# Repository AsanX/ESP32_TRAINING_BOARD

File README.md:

# ESP32_TRAINING_BOARD

ESP32 Training board is designed to have multiple things to play with so there are lot's of opportunities to learn the ESP32.
I made this board so i can remotely open our front door from 4th floor and figured i could do something else with it too.

- USB-C Charging, programming and serial monitor
- 18650 Battery with commonly used TP4056 charging circuit
- RGB Led
- Button / Encoder
- TMP100 12Bit I2C Temperature sensor
- OLED I2C Display
- Few optocoupler for inputs and outputs

# Alredy found mistakes from HW 1.0
## Enable pin and auto reset
When using automatic reset for programming, there needs to be a uF range capacitor on enable.
This is to make sure the IO0 pin is given some time to pull low to enter the download mode before the en pin gets HIGH.

## TP4056 temperature pin
Datasheet clearly says that the pin should be pulled low if there are no temperature sensor on the battery

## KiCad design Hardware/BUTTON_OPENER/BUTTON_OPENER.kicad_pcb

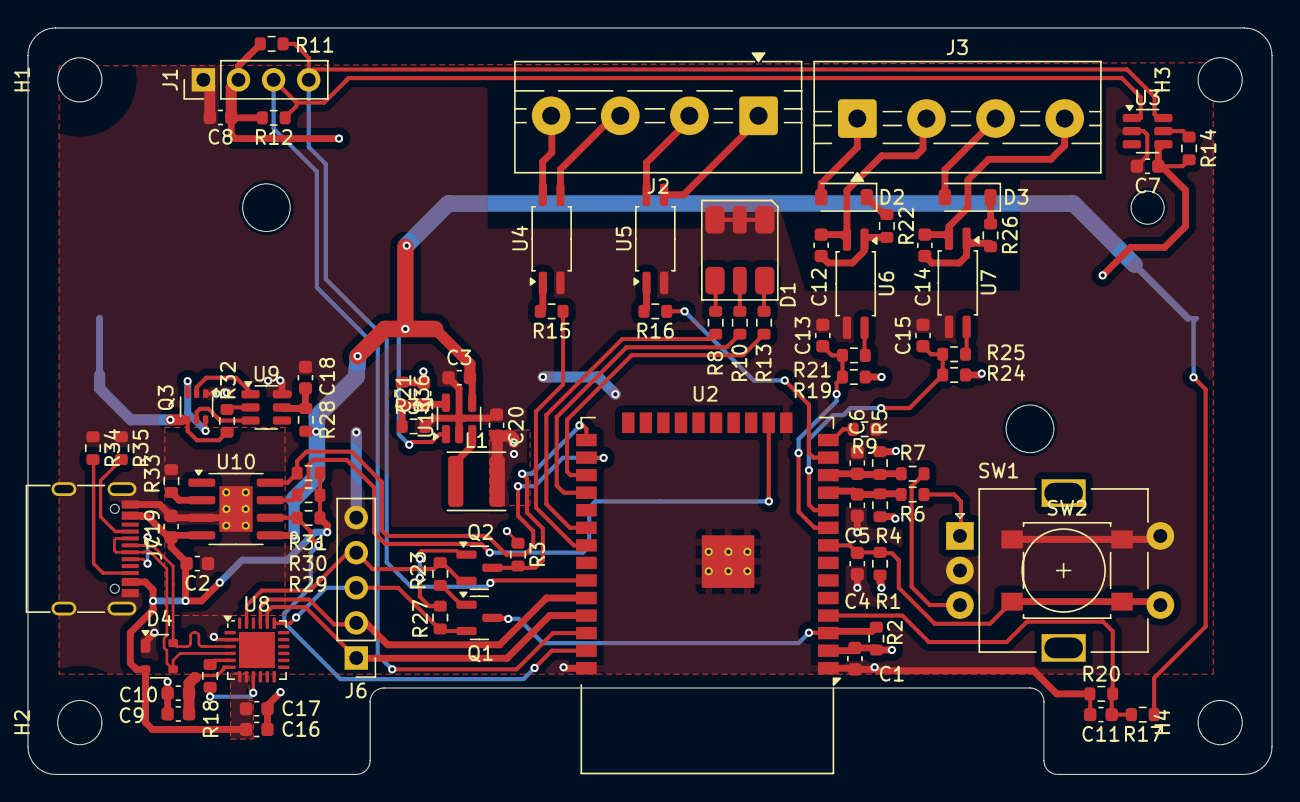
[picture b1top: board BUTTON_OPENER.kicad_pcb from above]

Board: 2 copper layers, 90.0 x 54.0 mm, 88 parts (1 on the bottom side), 67 nets.

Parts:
BT1: 18650 holder; BatteryHolder_Keystone_1042_1x18650
C1, C3, C20: 10uF 6.3V X7R; C_0603_1608Metric
C2: 1uF 10V X7R; C_0603_1608Metric
C4, C5, C6, C7, C8, C10, C11, C12, C13, C14, C15, C17, C18, C19: 100nF 10V X7R; C_0603_1608Metric
C9, C16: 4.7uF 10V X7R; C_0603_1608Metric
C21: 22pF; C_0603_1608Metric
D1: Inolux_IN-P55TATRGB; LED_Inolux_IN-P55TATRGB_PLCC6_5.0x5.5mm_P1.8mm
D2, D3: D; D_SOD-123
D4: SP0503BAHT; SOT-143
H1, H2, H3, H4: MountingHole; MountingHole_3.2mm_M3
J1: N/A; PinHeader_1x04_P2.54mm_Vertical
J2, J3: Screw_Terminal_01x04; TerminalBlock_MaiXu_MX126-5.0-04P_1x04_P5.00mm
J6: Conn_01x05; PinHeader_1x05_P2.54mm_Vertical
J7: USB_C_Receptacle_USB2.0_14P; USB_C_Receptacle_G-Switch_GT-USB-7010ASV
L1: 2.2uH; L_APV_ANR4020
Q1, Q2: BC847; SOT-23
Q3: BSD840N; SOT-363_SC-70-6
R1, R22, R26: 10K; R_0603_1608Metric
R2, R3, R9, R17: 33K; R_0603_1608Metric
R4, R5: 6K8; R_0603_1608Metric
R6, R7, R8, R13, R15, R16, R18, R21, R25, R32: 1K; R_0603_1608Metric
R10: 1K5; R_0603_1608Metric
R11, R12: 3K3; R_0603_1608Metric
R14, R19, R24, R29, R30: 47K; R_0603_1608Metric
R20: 8K2; R_0603_1608Metric
R23, R27: 12K; R_0603_1608Metric
R28: 100R; R_0603_1608Metric
R31: 0R; R_0603_1608Metric
R33: 2K2; R_0603_1608Metric
R34, R35: 5K1; R_0603_1608Metric
R36: 540K; R_0603_1608Metric
R37: 120K; R_0603_1608Metric
SW1: N/A; RotaryEncoder_Alps_EC11E-Switch_Vertical_H20mm
SW2: SW_Push; SW_SPST_B3S-1000
U2: ESP32-WROOM; ESP32-WROOM-32D
U3: TMP100; SOT-23-6
U4, U5, U6, U7: TCMT1100; SOP-4_4.4x2.6mm_P1.27mm
U8: CP2102N; QFN-24-1EP_4x4mm_P0.5mm_EP2.6x2.6mm
U9: DW01A; SOT-23-6
U10: TP4056-42-ESOP8; SOIC-8-1EP_3.9x4.9mm_P1.27mm_EP2.41x3.3mm_ThermalVias
U11: SUNTEK SK6615CS5; SOT-23-5

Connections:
+3V3: C1.2, C7.1, C8.1, C20.2, C21.2, J1.2, L1.2, R1.1, R2.1, R3.1, R4.1, R5.1, R11.2, R12.2, R14.2, R19.2, R24.2, R36.1, U2.2 (VDD), U3.4 (V+)
/B: R13.1, U2.27 (IO16)
/CHRG: R30.1, U2.16 (IO13), U10.7 (~CHRG)
/D+: D4.4 (K), J7.A6 (D+), J7.B6 (D+), U8.3 (D+)
/D-: D4.3 (K), J7.A7 (D-), J7.B7 (D-), U8.4 (D-)
/DTR: J6.4, Q2.2 (E), R23.1, U8.23 (~DTR)
/EN: R31.1, U2.26 (IO4), U10.8 (CE)
/ENABLE: Q1.3 (C), R2.2, U2.3 (EN)
/ENC_A: C5.2, R4.2, R6.2, U2.11 (IO26)
/ENC_B: C6.2, R5.2, R7.2, U2.12 (IO27)
/ENC_SW: C4.2, R1.2, SW1.S1, SW2.2, U2.8 (IO32)
/G: R10.1, U2.28 (IO17)
/GPIO0: Q2.3 (C), R3.2, U2.25 (IO0)
/OPTO_1: R15.1, U2.31 (IO19)
/OPTO_2: R16.1, U2.13 (IO14)
/OPTO_IN1: C13.1, R19.1, R21.2, U2.9 (IO33)
/OPTO_IN2: C15.1, R24.1, R25.2, U2.10 (IO25)
/R: R8.1, U2.30 (IO18)
/RTS: J6.3, Q1.2 (E), R27.1, U8.19 (~RTS)
/RXD: J6.2, U2.34 (RXD0/IO3), U8.21 (TXD)
/SCL: J1.3, R12.1, U2.36 (IO22), U3.1 (SCL)
/SDA: J1.4, R11.1, U2.33 (IO21), U3.6 (SDA)
/STDBY: R29.1, U2.37 (IO23), U10.6 (~STDBY)
/TXD: J6.1, U2.35 (TXD0/IO1), U8.20 (RXD)
/VBAT: BT1.1 (+), C3.2, R17.1, R28.2, U10.5 (BAT), U11.1 (EN), U11.4 (VIN)
/VBAT_AN: C11.1, R17.2, R20.1, U2.4 (SENSOR_VP)
/VBUS: C2.2, C16.2, C17.1, C19.1, D4.2 (K), J7.A4 (VBUS), J7.A9 (VBUS), J7.B4 (VBUS), J7.B9 (VBUS), R29.2, R30.2, R31.2, U8.7 (VREGIN), U8.8 (VBUS), U10.4 (V_{CC})
GND: C1.1, C2.1, C3.1, C4.1, C5.1, C6.1, C7.2, C8.2, C9.1, C10.2, C11.2, C13.2, C15.2, C16.1, C17.2, C18.2, C19.2, C20.1, D1.1 (KB), D1.2 (KR), D1.3 (KG), D4.1 (A), J1.1, J6.5, J7.A1 (GND), J7.A12 (GND), J7.B1 (GND), J7.B12 (GND), J7.S1 (SHIELD), Q3.1 (S), R9.2, R20.2, R33.1, R34.1, R35.1, R37.2, SW1.C, SW1.S2, SW2.1, U2.1 (GND), U2.15 (GND), U2.38 (GND), U2.39 (GND), U3.2 (GND), U4.2, U5.2, U6.3, U7.3, U8.2 (GND), U8.25 (GND), U9.6 (GND), U10.3 (GND), U10.9 (EPAD), U11.2 (GND)
unnamed: BT1.2 (-), Q3.4 (S), R32.1
unnamed: C12.1, R22.2, U6.1
unnamed: C14.1, R26.2, U7.1
unnamed: D1.6 (AB), R13.2
unnamed: D1.4 (AG), R8.2
unnamed: D1.5 (AR), R10.2
unnamed: D2.2 (A), J3.1
unnamed: D2.1 (K), R22.1
unnamed: D3.2 (A), J3.3
unnamed: D3.1 (K), R26.1
unnamed: J2.1, U5.3
unnamed: J2.2, U5.4
unnamed: J2.3, U4.3
unnamed: J2.4, U4.4
unnamed: C12.2, J3.2, U6.2
unnamed: C14.2, J3.4, U7.2
unnamed: J7.A5 (CC1), R35.2
unnamed: J7.B5 (CC2), R34.2
unnamed: Q1.1 (B), R23.2
unnamed: Q2.1 (B), R27.2
unnamed: Q3.3 (D), Q3.6 (D)
unnamed: Q3.2 (G), U9.1 (OD)
unnamed: Q3.5 (G), U9.3 (OC)
unnamed: R6.1, SW1.A
unnamed: R7.1, SW1.B
unnamed: R15.2, U4.1
unnamed: R16.2, U5.1
unnamed: R21.1, U6.4
unnamed: R25.1, U7.4
unnamed: R9.1, U2.14 (IO12)
unnamed: R14.1, U3.5 (ADD0)
unnamed: C9.2, C10.1, U8.6 (VDD)
unnamed: R18.1, U8.5 (VIO)
unnamed: R18.2, U8.9 (~RST)
unnamed: R32.2, U9.2 (CS)
unnamed: C18.1, R28.1, U9.5 (VCC)
unnamed: R33.2, U10.2 (PROG)
unnamed: C21.1, R36.2, R37.1, U11.5 (FB)
unnamed: L1.1, U11.3 (SW)

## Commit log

2025-08-08 Hardware
2025-08-08 Updated HW
2025-08-09 Update
    Connectors to screw terminals
    Regulator to low dropout buck
    USB C CC Resistors
    IO2 pulldown resistor added
2025-08-10 PCB ordered with this commit
2025-08-27 Test software
    - Oled
    - LEDs
    - Charger status
    - Battery voltage to oled
2025-08-27 Temp sensor
    Trying to make the TMP100 work with LM75 derived driveer but its printing -0.06c
2025-08-31 Working prototype of master / slave
    This code is pretty much from the ESP api.
2025-08-31 Update README.md
    Update README.md
